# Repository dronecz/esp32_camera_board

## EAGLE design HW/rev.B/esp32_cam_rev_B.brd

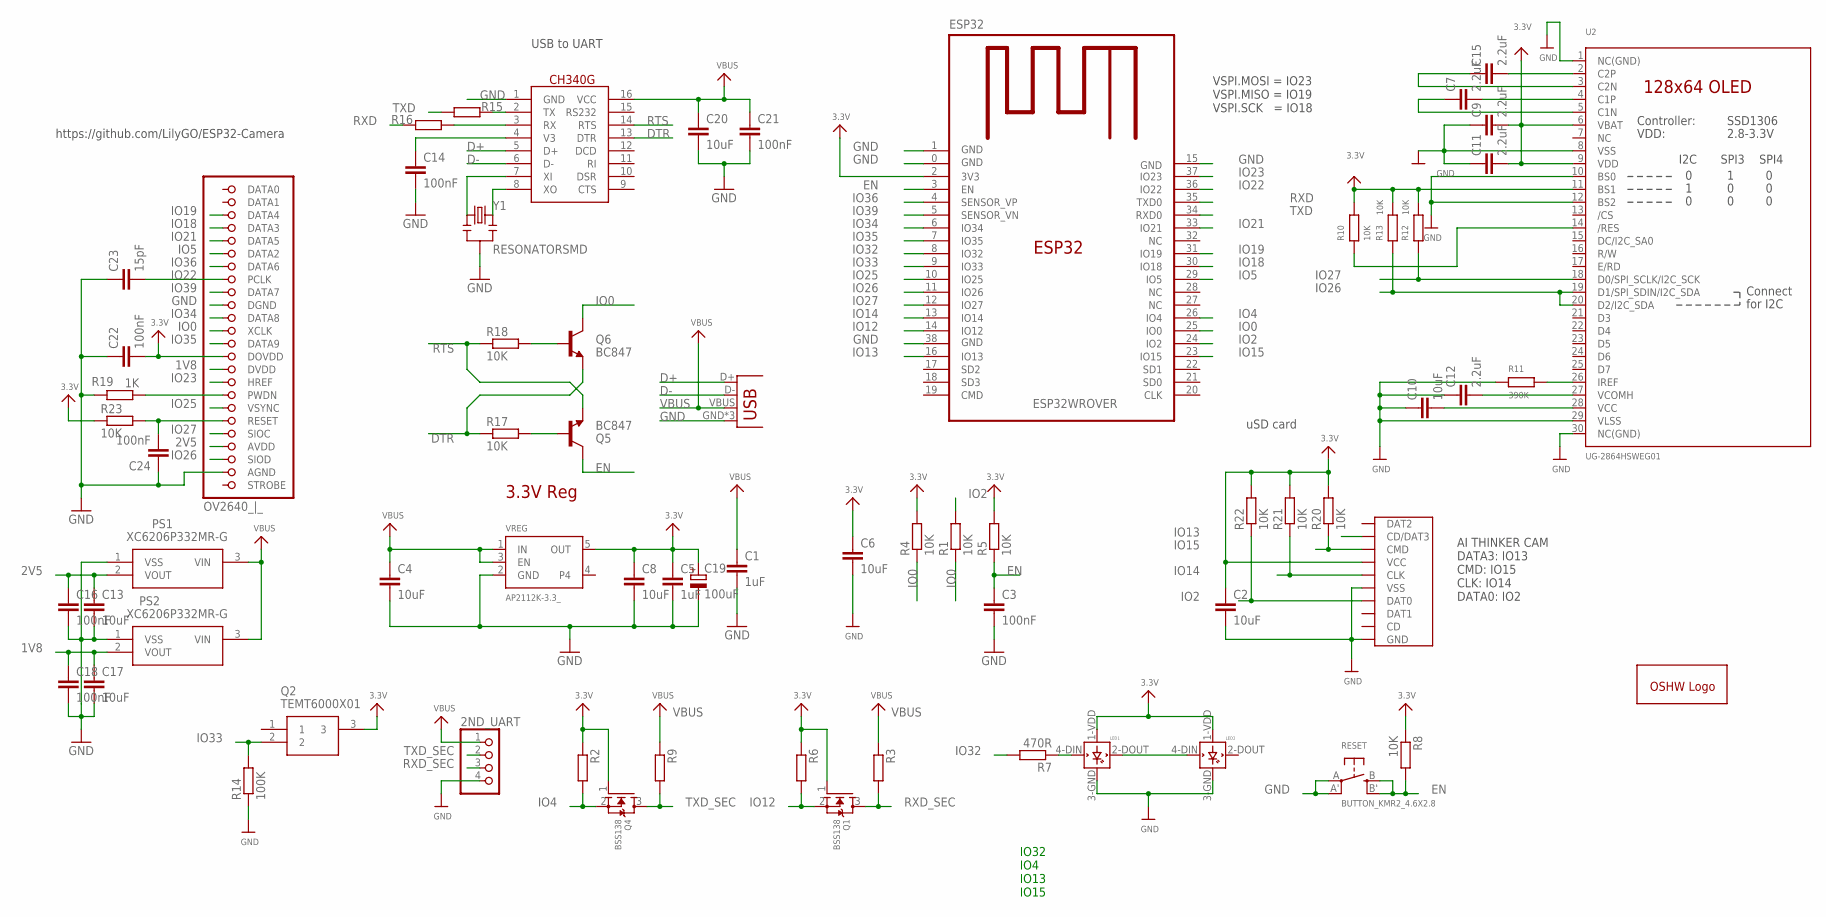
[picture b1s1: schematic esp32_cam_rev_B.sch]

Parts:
2ND_UART: JST_PH4; JSTPH4
C1: 1uF; C0805K
C2, C4, C8, C10, C13, C17, C20: 10uF; C0805
C3, C14: 100nF; C0805K
C5: 1uF; C0805
C6: 10uF; C0805K
C7, C9, C11, C12, C15: 2.2uF; C0805
C16, C18, C21, C22, C24: 100nF; C0805
C19: 100uF; CT6032
C23: 15pF; C0805
CH340G: CH340G; SO16
ESP32: ESP32WROVER
FPC_CONNECTOR: OV2640_|_; 5051102491
GOLD_ORB_SM1: OSHWLOGO_; OSHW_5MM_LOGO
LED1, LED2: WS2812B; WS2812B_5050
PS1, PS2: XC6206P332MR-G; SOT95P280X130-3N
Q1, Q4: BSS138; SOT95P240X110-3
Q2: TEMT6000X01
Q5, Q6: BC847; SOT23-3
R1, R2, R3, R4, R5, R6, R8, R9, R10, R12, R13, R17, R18, R20, R21, R22, R23: 10K; R0805
R7, R15, R16: 470R; R0805
R11: 390K; R0805
R14: 100K; R0805
R19: 1K; R0805
RESET: BUTTON_KMR2_4.6X2.8
SD_CARD: MICRO_SD_CARD_; TFP09-2--12B
U2: UG-2864HSWEG01; UG-2864HSWEG01_1.3_WRAPAROUND_MIRRORED
USB: USB_MICRO_ATTEND_; USB_MICRO
VREG: AP2112K-3.3_; SOT95P290X120-5
Y1: RESONATORSMD; RESONATOR-SMD

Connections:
1V8: C17.1, C18.1, FPC_CONNECTOR.15 (DVDD), PS2.2 (VOUT)
2V5: C13.1, C16.1, FPC_CONNECTOR.21 (AVDD), PS1.2 (VOUT)
3.3V: C2.1, C5.1, C6.1, C8.1, C9.2, C11.2, C19.+, C22.2, ESP32.2 (3V3), FPC_CONNECTOR.14 (DOVDD), LED1.1-VDD (VDD), LED2.1-VDD (VDD), Q1.1 (G), Q2.3, Q4.1 (G), R2.1, R4.2, R5.2, R6.1, R8.1, R10.2, R12.2, R13.2, R20.2, R21.2, R22.2, R23.1, SD_CARD.VCC, U2.6 (VBAT), U2.9 (VDD), U2.11 (BS1), VREG.5 (OUT)
D+: CH340G.5 (D+), USB.D+
D-: CH340G.6 (D-), USB.D-
DTR: CH340G.13 (DTR), Q6.2 (E), R17.1
EN: C3.1, ESP32.3 (EN), Q5.3 (C), R5.1, R8.2, RESET.B (S), RESET.B' (S1)
GND: 2ND_UART.4, C1.2, C2.2, C3.2, C4.2, C5.2, C6.2, C8.2, C9.1, C10.1, C11.1, C12.1, C13.2, C14.2, C16.2, C17.2, C18.2, C19.-, C20.2, C21.2, C22.1, C23.1, C24.1, CH340G.1 (GND), ESP32.0 (GND), ESP32.1 (GND), ESP32.15 (GND), ESP32.38 (GND), FPC_CONNECTOR.10 (DGND), FPC_CONNECTOR.23 (AGND), LED1.3-GND (GND), LED2.3-GND (GND), PS1.1 (VSS), PS2.1 (VSS), R11.1, R14.1, R19.2, RESET.A, RESET.A' (P1), SD_CARD.GND, SD_CARD.GND@1 (GND), SD_CARD.GND@2 (GND), SD_CARD.GND@3 (VSS), SD_CARD.VSS (GND), U2.1 (NC(GND)), U2.8 (VSS), U2.10 (BS0), U2.12 (BS2), U2.29 (VLSS), U2.30 (NC(GND)), USB.GND, USB.GND@2 (GND), USB.GND@3 (GND), VREG.2 (GND), Y1.2
IO0: ESP32.25 (IO0), FPC_CONNECTOR.12 (XCLK), Q6.3 (C), R1.1, R4.1
IO2: ESP32.24 (IO2), R1.2, R22.1, SD_CARD.DAT0
IO4: ESP32.26 (IO4), Q4.2 (S), R2.2
IO5: ESP32.29 (IO5), FPC_CONNECTOR.6 (DATA2)
IO12: ESP32.14 (IO12), Q1.2 (S), R6.2
IO13: ESP32.16 (IO13), SD_CARD.CD/DAT3
IO14: ESP32.13 (IO14), R21.1, SD_CARD.CLK
IO15: ESP32.23 (IO15), R20.1, SD_CARD.CMD
IO18: ESP32.30 (IO18), FPC_CONNECTOR.4 (DATA3)
IO19: ESP32.31 (IO19), FPC_CONNECTOR.3 (DATA4)
IO21: ESP32.33 (IO21), FPC_CONNECTOR.5 (DATA5)
IO22: C23.2, ESP32.36 (IO22), FPC_CONNECTOR.8 (PCLK)
IO23: ESP32.37 (IO23), FPC_CONNECTOR.16 (HREF)
IO25: ESP32.10 (IO25), FPC_CONNECTOR.18 (VSYNC)
IO26: ESP32.11 (IO26), FPC_CONNECTOR.22 (SIOD), R13.1, U2.19 (D1/SPI_SDIN/I2C_SDA), U2.20 (D2/I2C_SDA)
IO27: ESP32.12 (IO27), FPC_CONNECTOR.20 (SIOC), R12.1, U2.18 (D0/SPI_SCLK/I2C_SCK)
IO32: ESP32.8 (IO32), R7.2
IO33: ESP32.9 (IO33), Q2.2, R14.2
IO34: ESP32.6 (IO34), FPC_CONNECTOR.11 (DATA8)
IO35: ESP32.7 (IO35), FPC_CONNECTOR.13 (DATA9)
IO36: ESP32.4 (SENSOR_VP), FPC_CONNECTOR.7 (DATA6)
IO39: ESP32.5 (SENSOR_VN), FPC_CONNECTOR.9 (DATA7)
unnamed: R10.1, U2.14 (/RES)
unnamed: LED1.4-DIN (DIN), R7.1
unnamed: LED1.2-DOUT (DOUT), LED2.4-DIN (DIN)
unnamed: R11.2, U2.26 (IREF)
unnamed: C15.2, U2.2 (C2P)
unnamed: CH340G.8 (XO), Y1.3
unnamed: C15.1, U2.3 (C2N)
unnamed: C7.2, U2.4 (C1P)
unnamed: C7.1, U2.5 (C1N)
unnamed: C10.2, U2.28 (VCC)
unnamed: C12.2, U2.27 (VCOMH)
unnamed: CH340G.7 (XI), Y1.1
unnamed: C14.1, CH340G.4 (V3)
unnamed: CH340G.2 (TX), R15.1
unnamed: CH340G.3 (RX), R16.1
unnamed: Q5.1 (B), R17.2
unnamed: Q6.1 (B), R18.2
unnamed: FPC_CONNECTOR.17 (PWDN), R19.1
unnamed: C24.2, FPC_CONNECTOR.19 (RESET), R23.2
RTS: CH340G.14 (RTS), Q5.2 (E), R18.1
RXD: ESP32.35 (TXD0), R16.2
RXD_SEC: 2ND_UART.3, Q1.3 (D), R3.2
TXD: ESP32.34 (RXD0), R15.2
TXD_SEC: 2ND_UART.2, Q4.3 (D), R9.2
VBUS: 2ND_UART.1, C1.1, C4.1, C20.1, C21.1, CH340G.16 (VCC), PS1.3 (VIN), PS2.3 (VIN), R3.1, R9.1, USB.VBUS, VREG.1 (IN), VREG.3 (EN)

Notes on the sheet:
USB to UART
VSPI.MOSI = IO23 VSPI.MISO = IO19 VSPI.SCK = IO18
3.3V Reg
uSD card
https://github.com/LilyGO/ESP32-Camera
AI THINKER CAM DATA3: IO13 CMD: IO15 CLK: IO14 DATA0: IO2
IO32 IO4 IO13 IO15

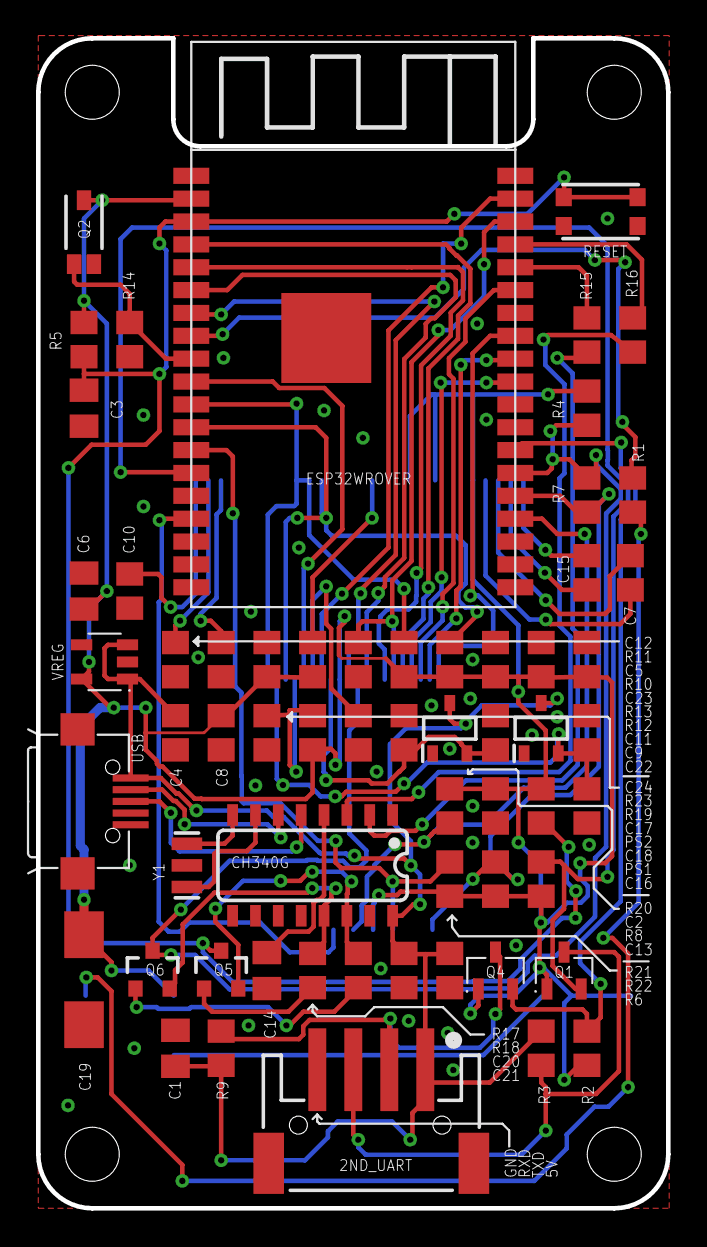
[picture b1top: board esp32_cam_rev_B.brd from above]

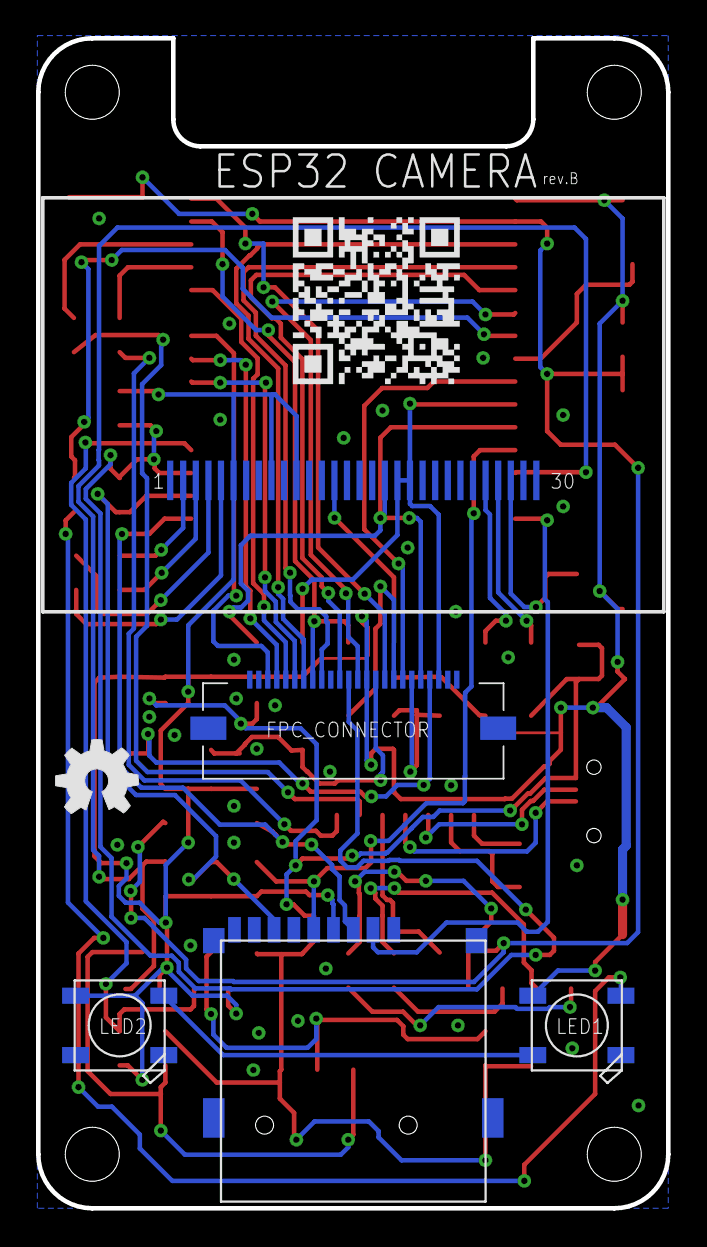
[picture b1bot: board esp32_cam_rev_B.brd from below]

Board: 2 copper layers, 35.0 x 65.0 mm, 67 parts (5 on the bottom side), 55 nets.

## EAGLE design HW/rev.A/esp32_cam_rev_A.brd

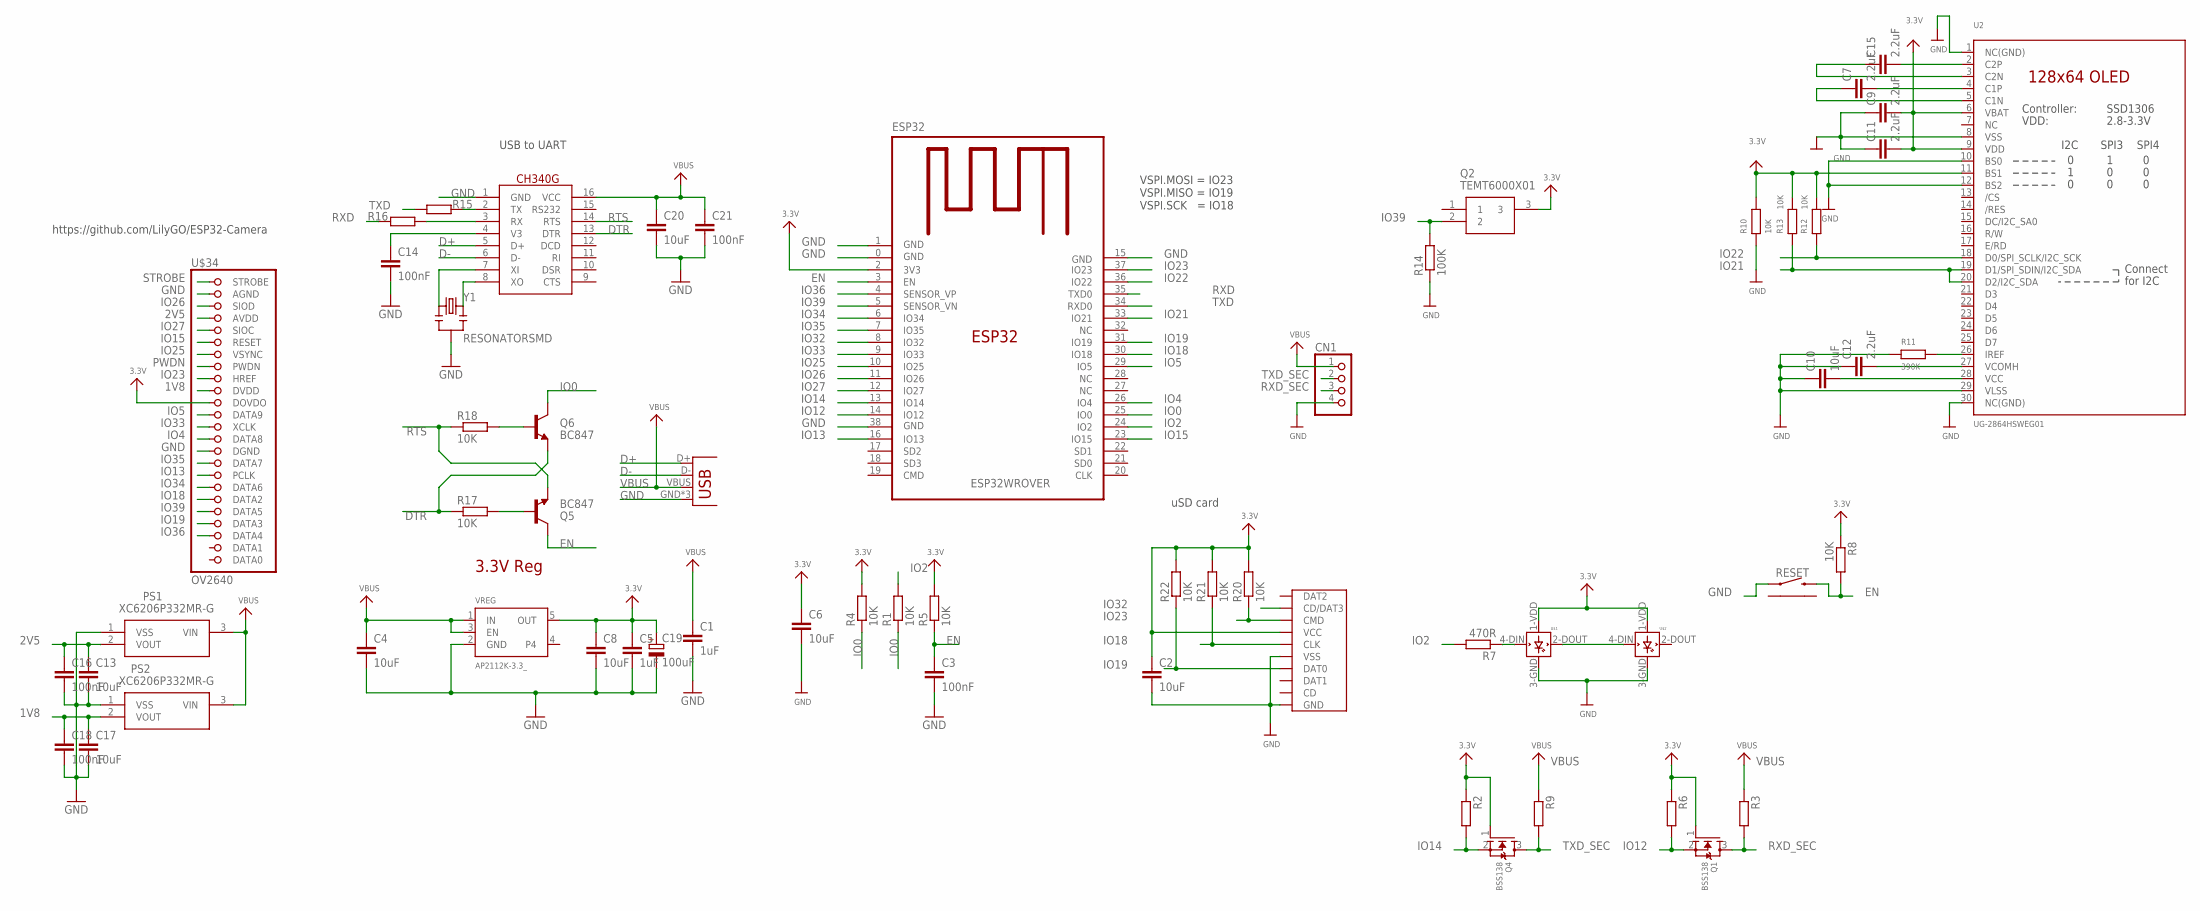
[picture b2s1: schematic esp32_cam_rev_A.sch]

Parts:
C1, C5: 1uF; C0805K
C2, C4, C6, C8, C13, C17, C20: 10uF; C0805K
C3, C14, C16, C18, C21: 100nF; C0805K
C7, C9, C11, C12, C15: 2.2uF; C0805
C10: 10uF; C0805
C19: 100uF; CT6032
CN1: JST_PH4; JSTPH4
ESP32: ESP32WROVER
PS1, PS2: XC6206P332MR-G; SOT95P280X130-3N
Q1, Q4: BSS138; SOT95P240X110-3
Q2: TEMT6000X01
Q5, Q6: BC847; SOT23-3
R1, R2, R3, R4, R5, R6, R8, R9, R10, R12, R13, R17, R18, R20, R21, R22: 10K; R0805
R7, R15, R16: 470R; R0805
R11: 390K; R0805
R14: 100K; R0805
RESET: TACTILE_SWITCH_RIGHT_ANGLE_THT"; TACTILE_SWITCH_RIGHT_ANGLE_THT
SD_CARD: MICRO_SD_CARD"; TFP09-2--12B
U2: UG-2864HSWEG01; UG-2864HSWEG01_1.3_WRAPAROUND_MIRRORED
U$1, U$2: WS2812B; WS2812B_5050
U$23: CH340G; SO16
U$34: OV2640; FH12-24S-0.5SH
USB: USB_MICRO_ATTEND_; USB_MICRO
VREG: AP2112K-3.3_; SOT95P290X120-5
Y1: RESONATORSMD; RESONATOR-SMD

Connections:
1V8: C17.1, C18.1, PS2.2 (VOUT), U$34.10 (DVDD)
2V5: C13.1, C16.1, PS1.2 (VOUT), U$34.4 (AVDD)
3.3V: C2.1, C5.1, C6.1, C8.1, C9.2, C11.2, C19.+, ESP32.2 (3V3), Q1.1 (G), Q2.3, Q4.1 (G), R2.1, R4.2, R5.2, R6.1, R8.1, R10.2, R12.2, R13.2, R20.2, R21.2, R22.2, SD_CARD.VCC, U2.6 (VBAT), U2.9 (VDD), U2.11 (BS1), U$1.1-VDD (VDD), U$2.1-VDD (VDD), U$34.11 (DOVDO), VREG.5 (OUT)
D+: U$23.5 (D+), USB.D+
D-: U$23.6 (D-), USB.D-
DTR: Q6.2 (E), R17.1, U$23.13 (DTR)
EN: C3.1, ESP32.3 (EN), Q5.3 (C), R5.1, R8.2, RESET.2
GND: C1.2, C2.2, C3.2, C4.2, C5.2, C6.2, C8.2, C9.1, C10.1, C11.1, C12.1, C13.2, C14.2, C16.2, C17.2, C18.2, C19.-, C20.2, C21.2, CN1.4, ESP32.0 (GND), ESP32.1 (GND), ESP32.15 (GND), ESP32.38 (GND), PS1.1 (VSS), PS2.1 (VSS), R10.1, R11.1, R14.1, RESET.1, SD_CARD.GND, SD_CARD.GND@1 (GND), SD_CARD.GND@2 (GND), SD_CARD.GND@3 (VSS), SD_CARD.VSS (GND), U2.1 (NC(GND)), U2.8 (VSS), U2.10 (BS0), U2.12 (BS2), U2.29 (VLSS), U2.30 (NC(GND)), U$1.3-GND (GND), U$2.3-GND (GND), U$23.1 (GND), U$34.2 (AGND), U$34.15 (DGND), USB.GND, USB.GND@2 (GND), USB.GND@3 (GND), VREG.2 (GND), Y1.2
IO0: ESP32.25 (IO0), Q6.3 (C), R1.1, R4.1
IO2: ESP32.24 (IO2), R1.2, R7.2
IO4: ESP32.26 (IO4), U$34.14 (DATA8)
IO5: ESP32.29 (IO5), U$34.12 (DATA9)
IO12: ESP32.14 (IO12), Q1.2 (S), R6.2
IO13: ESP32.16 (IO13), U$34.17 (PCLK)
IO14: ESP32.13 (IO14), Q4.2 (S), R2.2
IO15: ESP32.23 (IO15), U$34.6 (RESET)
IO18: ESP32.30 (IO18), R21.1, SD_CARD.CLK, U$34.19 (DATA2)
IO19: ESP32.31 (IO19), R22.1, SD_CARD.DAT0, U$34.21 (DATA3)
IO21: ESP32.33 (IO21), R13.1, U2.19 (D1/SPI_SDIN/I2C_SDA), U2.20 (D2/I2C_SDA)
IO22: ESP32.36 (IO22), R12.1, U2.18 (D0/SPI_SCLK/I2C_SCK)
IO23: ESP32.37 (IO23), R20.1, SD_CARD.CMD, U$34.9 (HREF)
IO25: ESP32.10 (IO25), U$34.7 (VSYNC)
IO26: ESP32.11 (IO26), U$34.3 (SIOD)
IO27: ESP32.12 (IO27), U$34.5 (SIOC)
IO32: ESP32.8 (IO32), SD_CARD.CD/DAT3
IO33: ESP32.9 (IO33), U$34.13 (XCLK)
IO34: ESP32.6 (IO34), U$34.18 (DATA6)
IO35: ESP32.7 (IO35), U$34.16 (DATA7)
IO36: ESP32.4 (SENSOR_VP), U$34.22 (DATA4)
IO39: ESP32.5 (SENSOR_VN), Q2.2, R14.2, U$34.20 (DATA5)
unnamed: R7.1, U$1.4-DIN (DIN)
unnamed: U$1.2-DOUT (DOUT), U$2.4-DIN (DIN)
unnamed: R11.2, U2.26 (IREF)
unnamed: C15.2, U2.2 (C2P)
unnamed: U$23.8 (XO), Y1.3
unnamed: C15.1, U2.3 (C2N)
unnamed: C7.2, U2.4 (C1P)
unnamed: C7.1, U2.5 (C1N)
unnamed: C10.2, U2.28 (VCC)
unnamed: C12.2, U2.27 (VCOMH)
unnamed: U$23.7 (XI), Y1.1
unnamed: C14.1, U$23.4 (V3)
unnamed: R15.1, U$23.2 (TX)
unnamed: R16.1, U$23.3 (RX)
unnamed: Q5.1 (B), R17.2
unnamed: Q6.1 (B), R18.2
PWDN: U$34.8 (PWDN)
RTS: Q5.2 (E), R18.1, U$23.14 (RTS)
RXD: ESP32.35 (TXD0), R16.2
RXD_SEC: CN1.3, Q1.3 (D), R3.2
STROBE: U$34.1 (STROBE)
TXD: ESP32.34 (RXD0), R15.2
TXD_SEC: CN1.2, Q4.3 (D), R9.2
VBUS: C1.1, C4.1, C20.1, C21.1, CN1.1, PS1.3 (VIN), PS2.3 (VIN), R3.1, R9.1, U$23.16 (VCC), USB.VBUS, VREG.1 (IN), VREG.3 (EN)

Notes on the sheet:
USB to UART
VSPI.MOSI = IO23 VSPI.MISO = IO19 VSPI.SCK = IO18
3.3V Reg
uSD card
https://github.com/LilyGO/ESP32-Camera

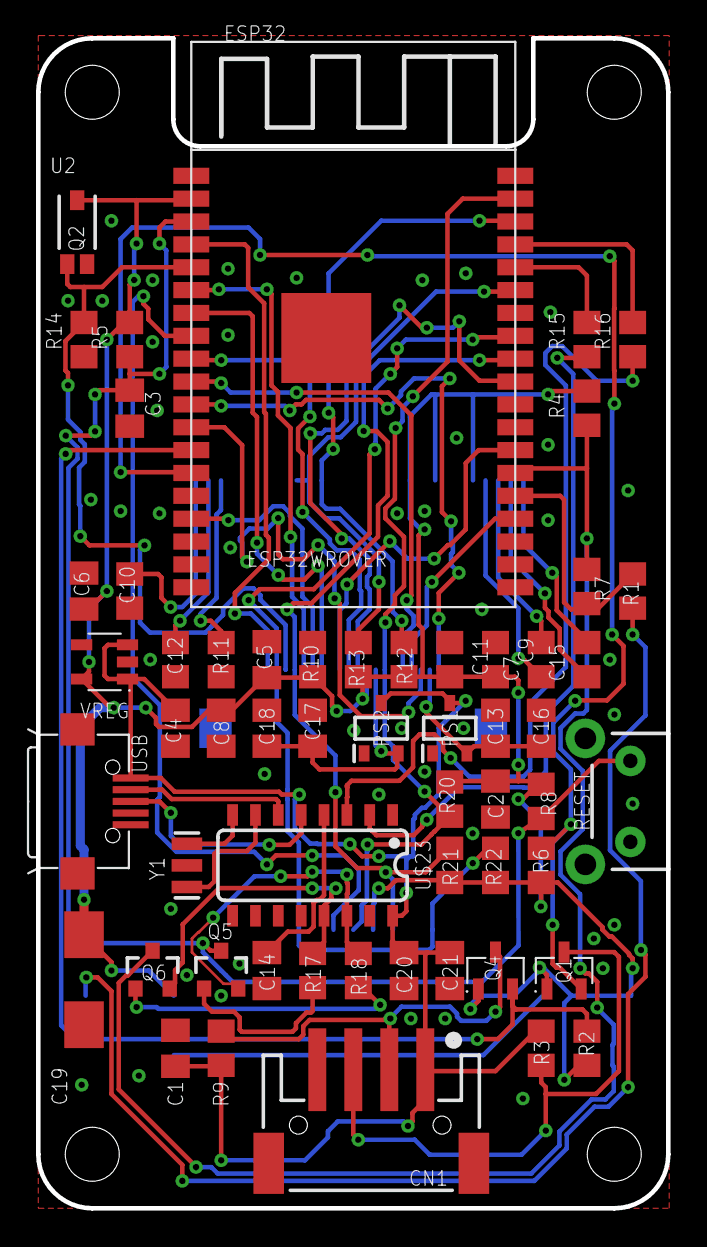
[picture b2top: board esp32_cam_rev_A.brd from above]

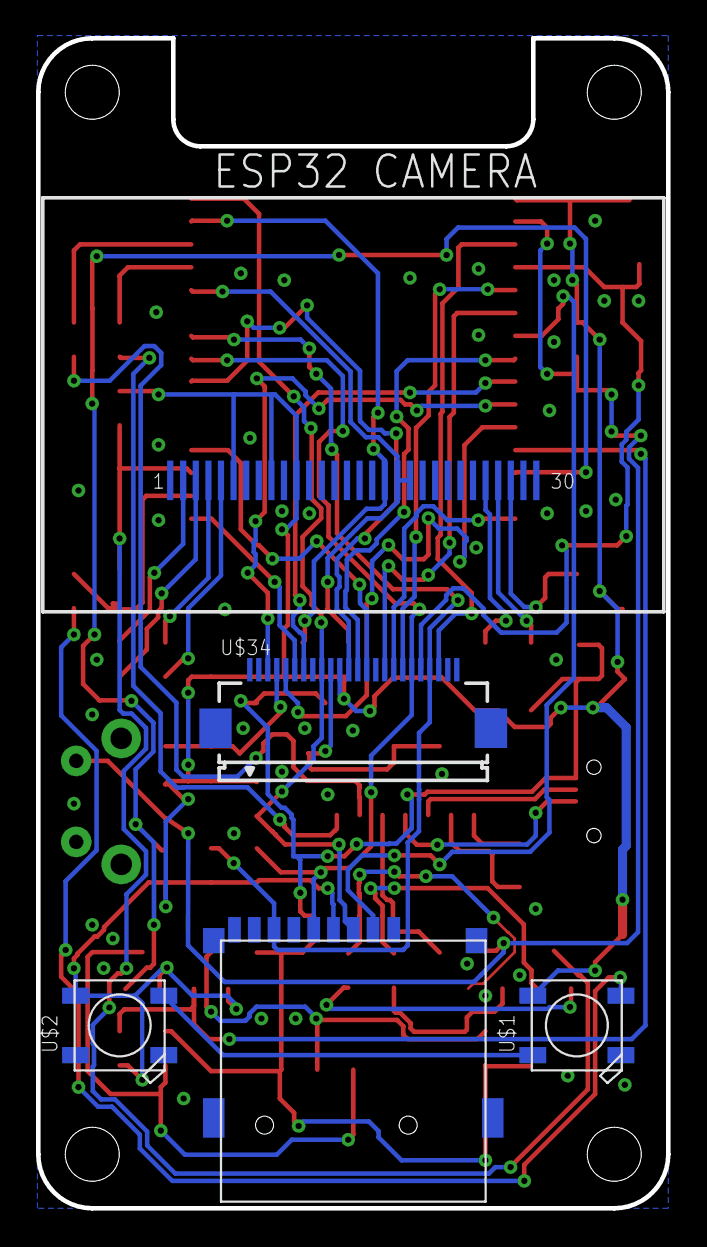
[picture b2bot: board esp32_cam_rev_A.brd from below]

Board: 2 copper layers, 35.0 x 65.0 mm, 61 parts (4 on the bottom side), 52 nets.

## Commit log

2019-10-09 First commit
    Initial commint of HW and FW

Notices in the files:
parts and their libraries:
microbuilder: This work is placed in the public domain, and may be freely used for commercial and non-commercial work with the following conditions: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
